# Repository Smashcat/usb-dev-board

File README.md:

# usb-dev-board
Development/testing board for various types of USB port. Pin headers to allow ports to be connected to eachother or to the on-board ATMega8u2 microcontroller with USB capability. The headers can also be useful to "sniff" signals going over USB between 2 devices, either using a scope, or passively using the onboard microcontroller!

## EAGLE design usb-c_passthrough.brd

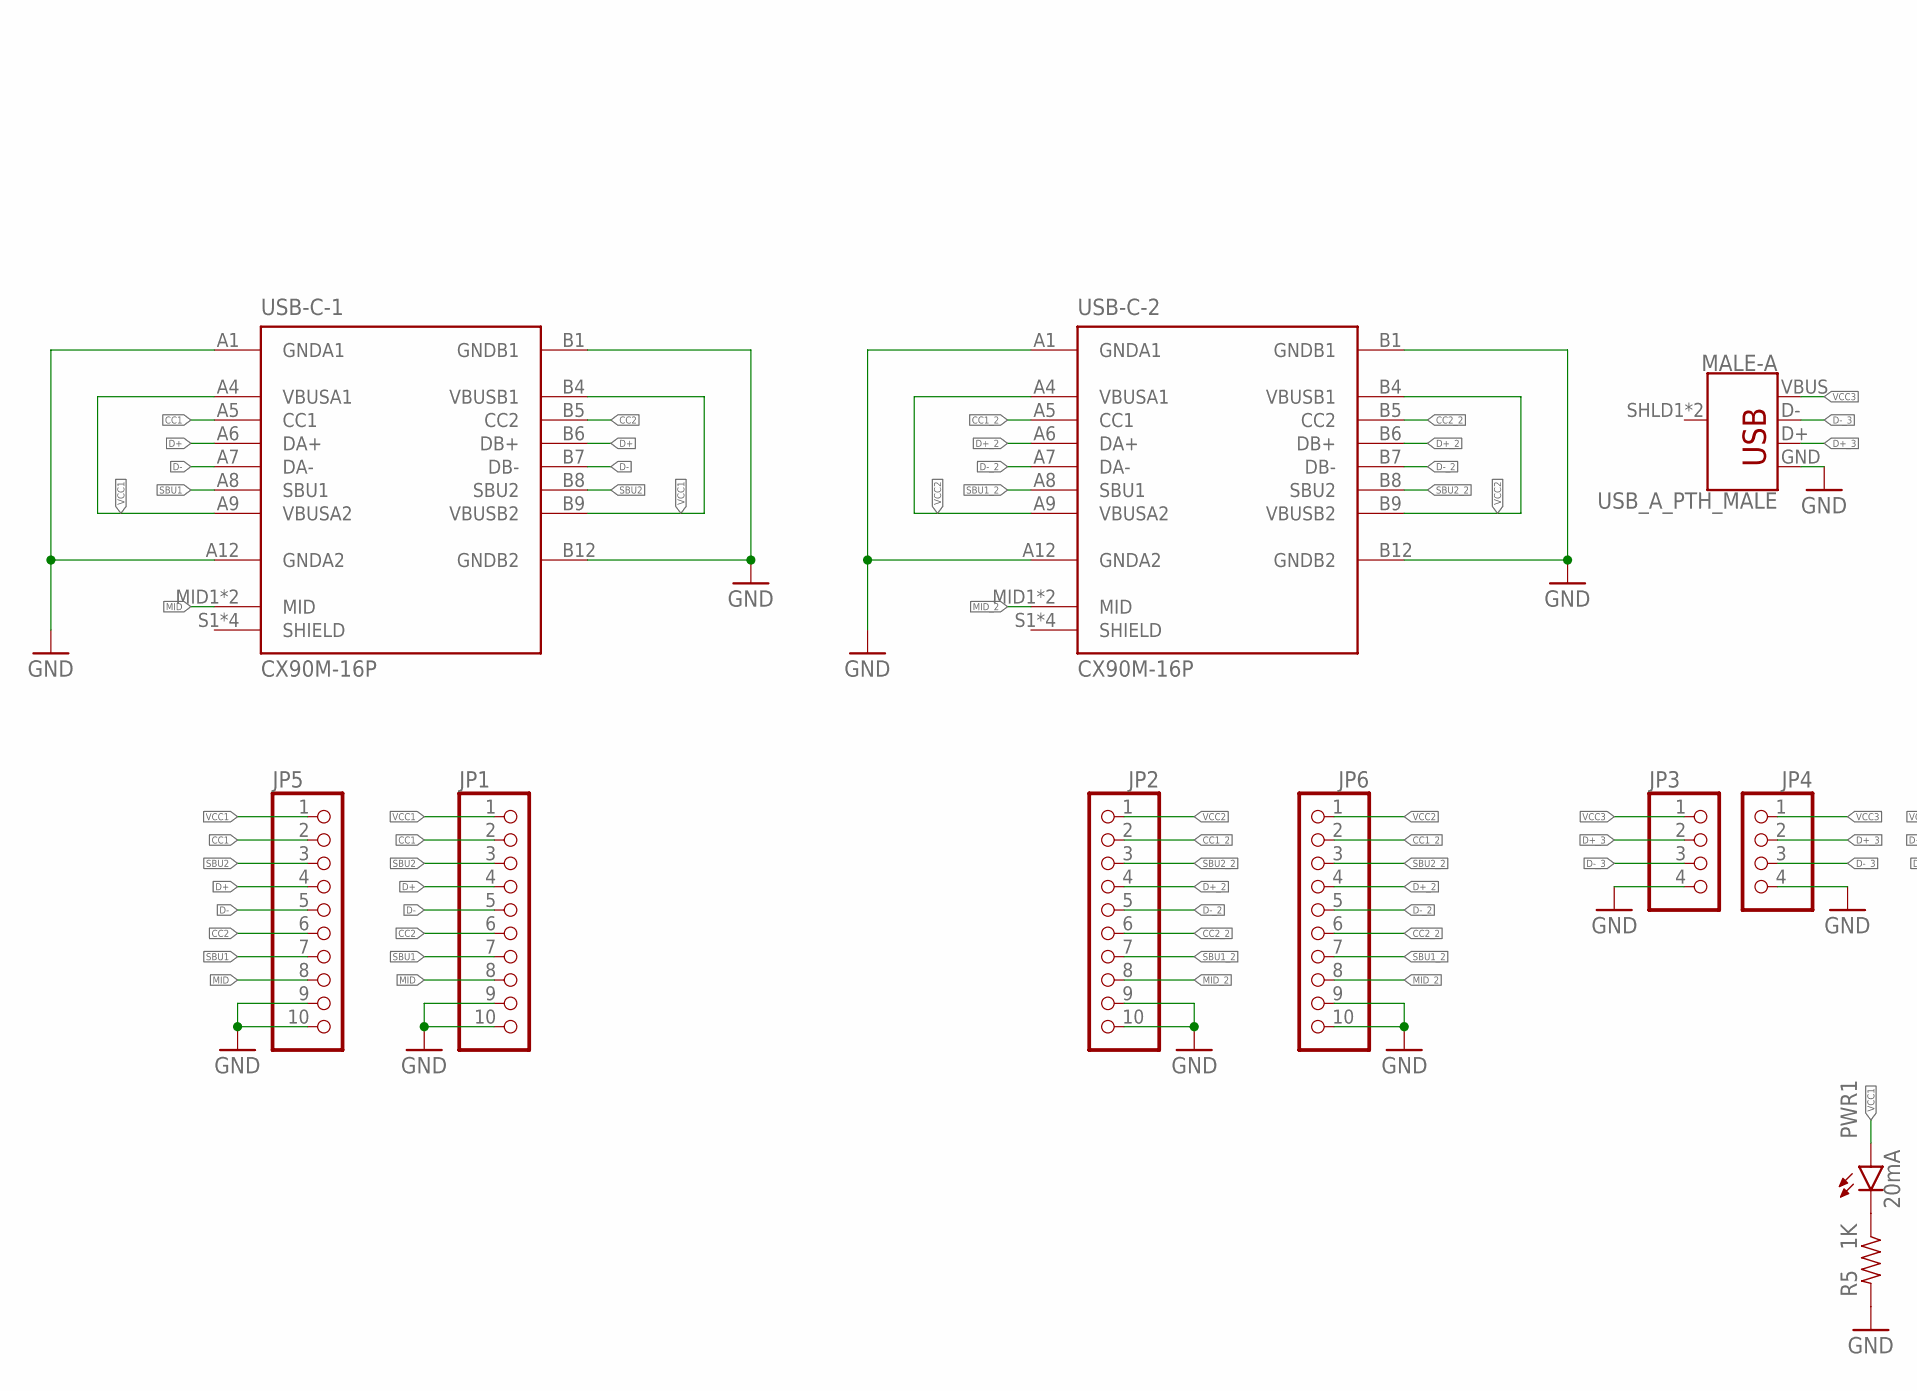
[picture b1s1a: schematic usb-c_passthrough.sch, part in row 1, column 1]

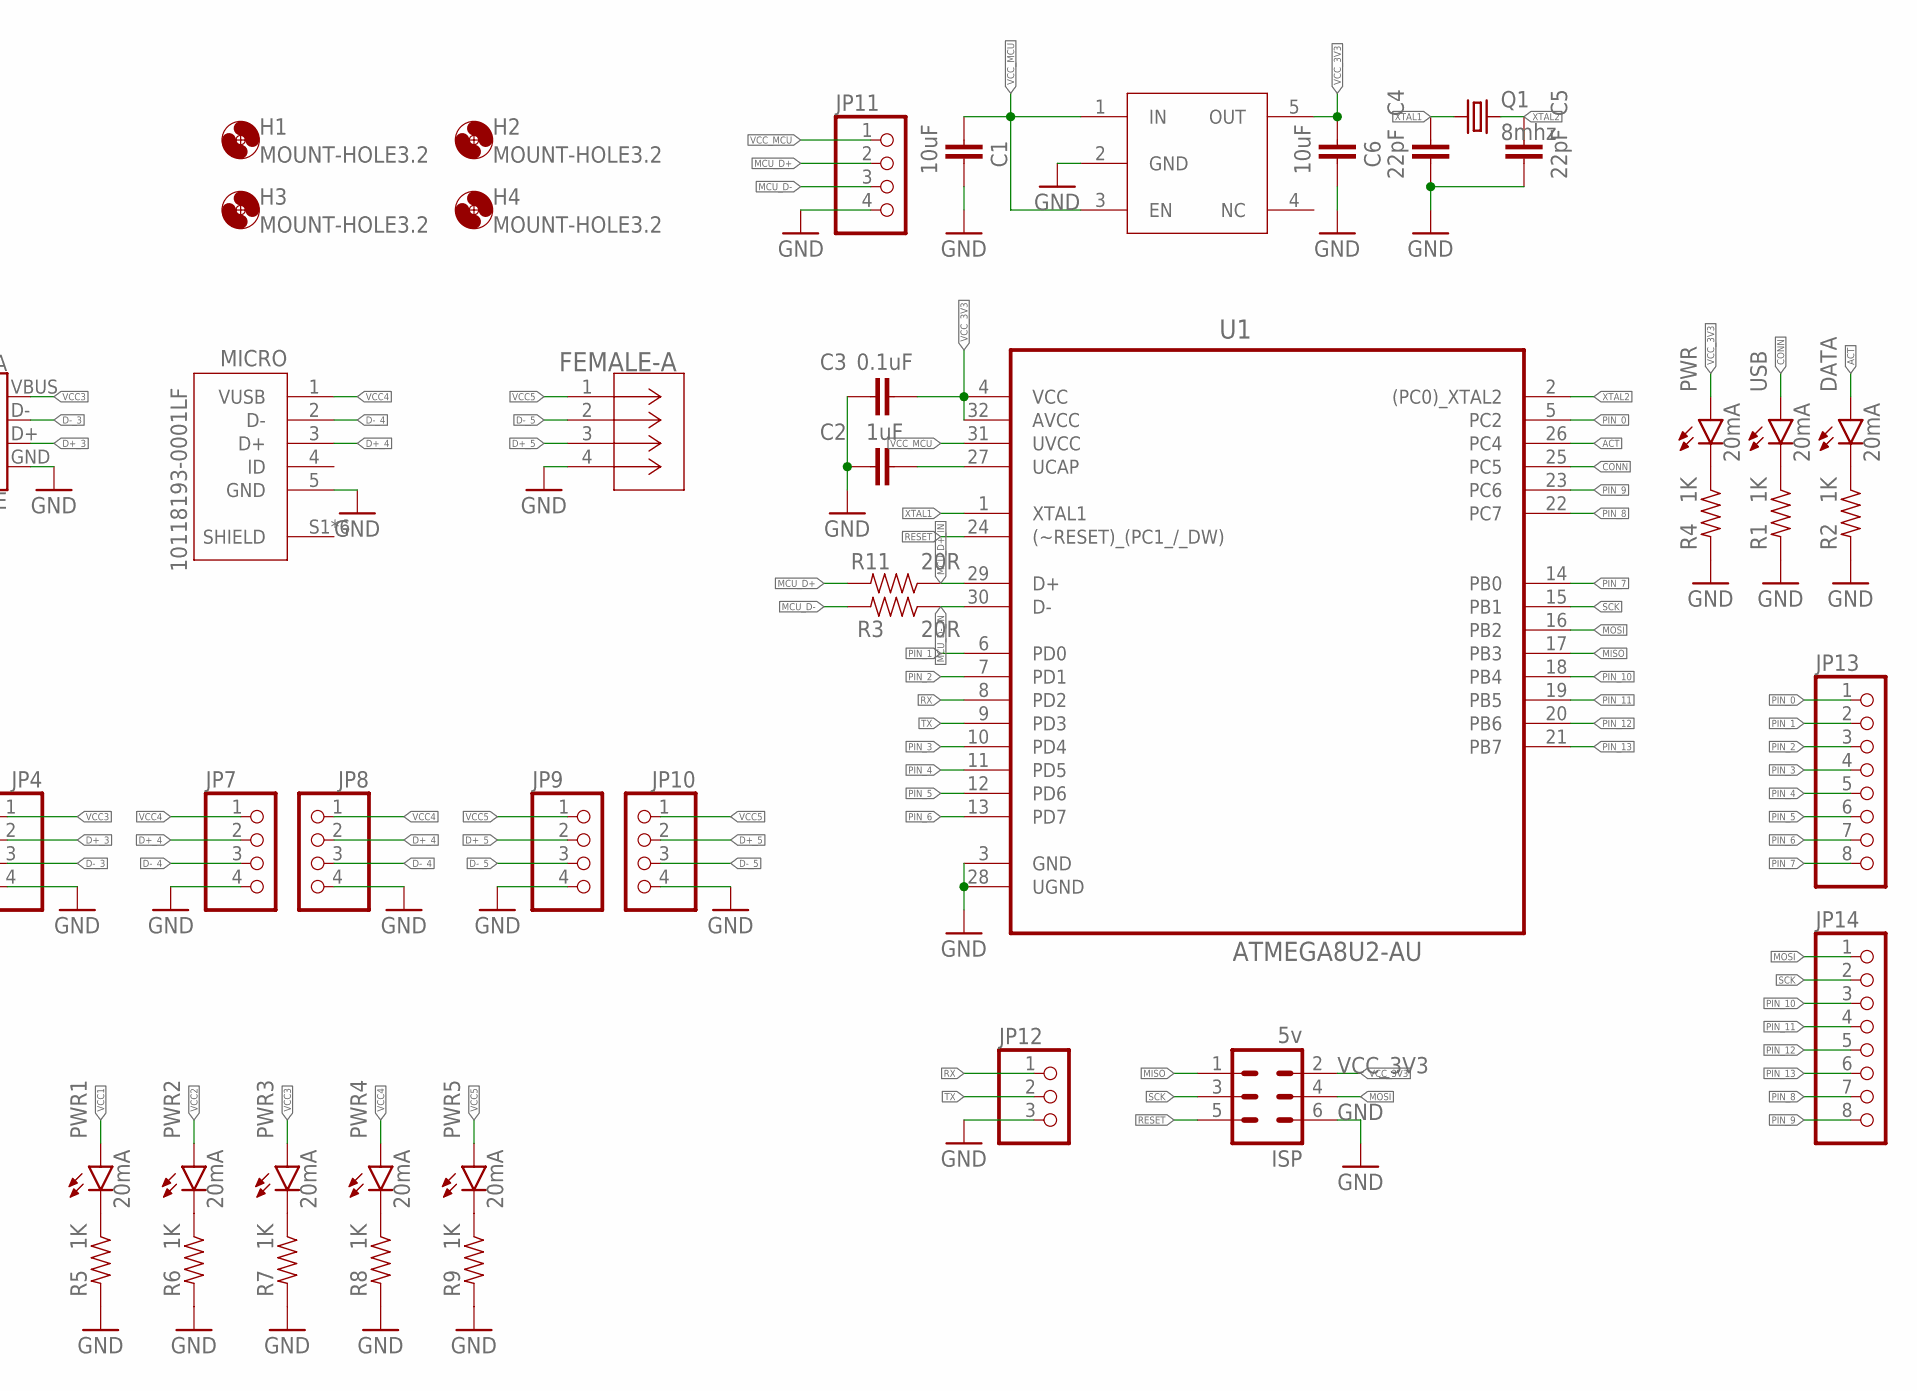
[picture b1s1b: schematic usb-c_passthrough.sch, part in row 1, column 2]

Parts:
3V3_REG: 3v3 LDO; NCP718BSN330T1G
C1, C6: 10uF; C0603
C2: 1uF; C0603
C3: 0.1uF; C0603
C4, C5: 22pF; C0603
DATA: 20mA; CHIP-LED0603
FEMALE-A: 292303-1; CONN_292303-1
H1, H2, H3, H4: MOUNT-HOLE3.2; 3,2
ISP: 5v; MA03-2
JP1, JP2, JP5, JP6: PINHD-1X10; 1X10
JP3, JP4, JP7, JP8, JP9, JP10, JP11: PINHD-1X4; 1X04
JP12: PINHD-1X3; 1X03
JP13, JP14: PINHD-1X8; 1X08
MALE-A: USB_A_PTH_MALE; USB-A-H
MICRO: 10118193-0001LF; FCI_10118193-0001LF
PWR, PWR1, PWR2, PWR3, PWR4, PWR5: 20mA; CHIP-LED0603
Q1: 8mhz; HC49UP
R1, R2, R4, R5, R6, R7, R8, R9: 1K; 0603
R3, R11: 20R; 0603
U1: ATMEGA8U2-AU; QFP80P900X900X120-32N
USB: 20mA; CHIP-LED0603
USB-C-1, USB-C-2: CX90M-16P; HRS_CX90M-16P

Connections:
ACT: DATA.A, U1.26 (PC4)
CC1: JP1.2, JP5.2, USB-C-1.A5 (CC1)
CC1_2: JP2.2, JP6.2, USB-C-2.A5 (CC1)
CC2: JP1.6, JP5.6, USB-C-1.B5 (CC2)
CC2_2: JP2.6, JP6.6, USB-C-2.B5 (CC2)
CONN: U1.25 (PC5), USB.A
D+: JP1.4, JP5.4, USB-C-1.A6 (DA+), USB-C-1.B6 (DB+)
D+_2: JP2.4, JP6.4, USB-C-2.A6 (DA+), USB-C-2.B6 (DB+)
D+_3: JP3.2, JP4.2, MALE-A.D+
D+_4: JP7.2, JP8.2, MICRO.3 (D+)
D+_5: FEMALE-A.3, JP9.2, JP10.2
D-: JP1.5, JP5.5, USB-C-1.A7 (DA-), USB-C-1.B7 (DB-)
D-_2: JP2.5, JP6.5, USB-C-2.A7 (DA-), USB-C-2.B7 (DB-)
D-_3: JP3.3, JP4.3, MALE-A.D-
D-_4: JP7.3, JP8.3, MICRO.2 (D-)
D-_5: FEMALE-A.2, JP9.3, JP10.3
GND: 3V3_REG.2 (GND), C1.1, C2.1, C3.1, C4.2, C5.2, C6.1, FEMALE-A.4 (GND), ISP.6, JP1.9, JP1.10, JP2.9, JP2.10, JP3.4, JP4.4, JP5.9, JP5.10, JP6.9, JP6.10, JP7.4, JP8.4, JP9.4, JP10.4, JP11.4, JP12.3, MALE-A.GND, MICRO.5 (GND), R1.2, R2.2, R4.2, R5.2, R6.2, R7.2, R8.2, R9.2, U1.3 (GND), U1.28 (UGND), USB-C-1.A1 (GNDA1), USB-C-1.A12 (GNDA2), USB-C-1.B1 (GNDB1), USB-C-1.B12 (GNDB2), USB-C-2.A1 (GNDA1), USB-C-2.A12 (GNDA2), USB-C-2.B1 (GNDB1), USB-C-2.B12 (GNDB2)
MCU_D+: JP11.2, R11.2
MCU_D+_IN: R11.1, U1.29 (D+)
MCU_D-: JP11.3, R3.2
MCU_D-_IN: R3.1, U1.30 (D-)
MID: JP1.8, JP5.8, USB-C-1.MID1 (MID), USB-C-1.MID2 (MID)
MID_2: JP2.8, JP6.8, USB-C-2.MID1 (MID), USB-C-2.MID2 (MID)
MISO: ISP.1, U1.17 (PB3)
MOSI: ISP.4, JP14.1, U1.16 (PB2)
unnamed: DATA.C, R2.1
unnamed: C2.2, U1.27 (UCAP)
unnamed: R1.1, USB.C
unnamed: PWR.C, R4.1
unnamed: PWR1.C, R5.1
unnamed: PWR2.C, R6.1
unnamed: PWR3.C, R7.1
unnamed: PWR4.C, R8.1
unnamed: PWR5.C, R9.1
PIN_0: JP13.1, U1.5 (PC2)
PIN_1: JP13.2, U1.6 (PD0)
PIN_2: JP13.3, U1.7 (PD1)
PIN_3: JP13.4, U1.10 (PD4)
PIN_4: JP13.5, U1.11 (PD5)
PIN_5: JP13.6, U1.12 (PD6)
PIN_6: JP13.7, U1.13 (PD7)
PIN_7: JP13.8, U1.14 (PB0)
PIN_8: JP14.7, U1.22 (PC7)
PIN_9: JP14.8, U1.23 (PC6)
PIN_10: JP14.3, U1.18 (PB4)
PIN_11: JP14.4, U1.19 (PB5)
PIN_12: JP14.5, U1.20 (PB6)
PIN_13: JP14.6, U1.21 (PB7)
RESET: ISP.5, U1.24 ((~RESET)_(PC1_/_DW))
RX: JP12.1, U1.8 (PD2)
SBU1: JP1.7, JP5.7, USB-C-1.A8 (SBU1)
SBU1_2: JP2.7, JP6.7, USB-C-2.A8 (SBU1)
SBU2: JP1.3, JP5.3, USB-C-1.B8 (SBU2)
SBU2_2: JP2.3, JP6.3, USB-C-2.B8 (SBU2)
SCK: ISP.3, JP14.2, U1.15 (PB1)
TX: JP12.2, U1.9 (PD3)
VCC1: JP1.1, JP5.1, PWR1.A, USB-C-1.A4 (VBUSA1), USB-C-1.A9 (VBUSA2), USB-C-1.B4 (VBUSB1), USB-C-1.B9 (VBUSB2)
VCC2: JP2.1, JP6.1, PWR2.A, USB-C-2.A4 (VBUSA1), USB-C-2.A9 (VBUSA2), USB-C-2.B4 (VBUSB1), USB-C-2.B9 (VBUSB2)
VCC3: JP3.1, JP4.1, MALE-A.VBUS, PWR3.A
VCC4: JP7.1, JP8.1, MICRO.1 (VUSB), PWR4.A
VCC5: FEMALE-A.1 (PWR), JP9.1, JP10.1, PWR5.A
VCC_3V3: 3V3_REG.5 (OUT), C3.2, C6.2, ISP.2, PWR.A, U1.4 (VCC), U1.32 (AVCC)
VCC_MCU: 3V3_REG.1 (IN), 3V3_REG.3 (EN), C1.2, JP11.1, U1.31 (UVCC)
XTAL1: C4.1, Q1.1, U1.1 (XTAL1)
XTAL2: C5.1, Q1.2, U1.2 ((PC0)_XTAL2)

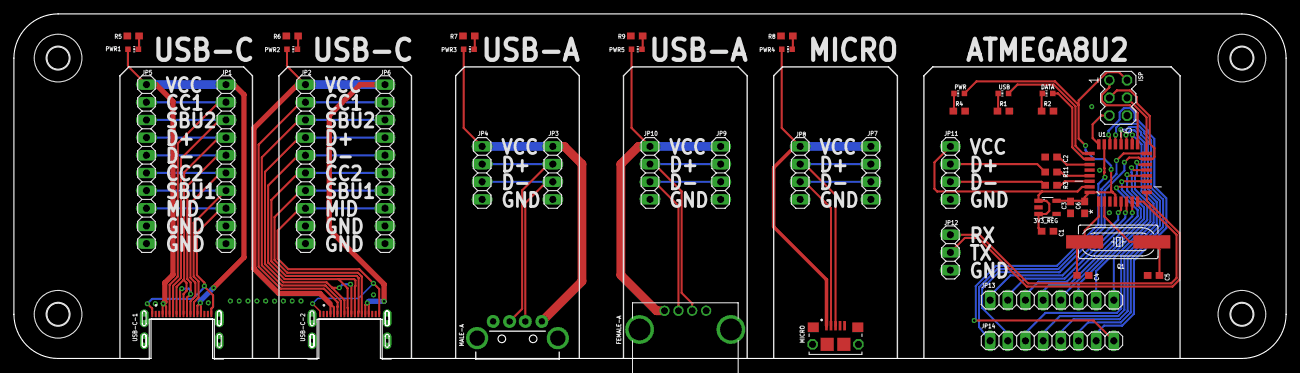
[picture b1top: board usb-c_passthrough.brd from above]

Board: 2 copper layers, 182.9 x 49.6 mm, 51 parts (0 on the bottom side), 65 nets.

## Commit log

2020-06-24 Added files
2020-06-24 Added photo

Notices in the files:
parts and their libraries:
SparkFun-Connectors: Licensing: Creative Commons ShareAlike 4.0 International - https://creativecommons.org/licenses/by-sa/4.0
